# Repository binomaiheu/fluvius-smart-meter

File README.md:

# Fluvius smart meter readout project

This is my version of a readout board for the Belgian smart energy meter deployed by Fluvius. The device contains 2 ports which allow the interested hobbyist to read out the real time energy consumption every sectond P1 and the full 4kHz waveform via the S1 port. This repo is for my own education as I shamelessly copied and adapted the work of Matthijs Kooijman and Willem Aandwiel, see links below for the originals !

## Links

Below is a collection of references with the original material upon which I based this **original project** : 
* https://willem.aandewiel.nl/index.php/2018/08/28/slimme-meter-uitlezer/
* https://opencircuit.nl/blog/Slimme-meter-uitlezer 

And a few links on **github** : 

* Decoder : https://github.com/matthijskooijman/arduino-dsmr
* Logger : https://github.com/mrWheel/DSMRlogger2HTTP
* https://mrwheel.github.io/DSMRloggerWS/

You can find a **python decoder** for the serial messages here : 
* https://github.com/jvhaarst/DSMR-P1-telegram-reader

The **specs** for the smart meter can be found here : 
* https://www.netbeheernederland.nl/_upload/Files/Slimme_meter_15_a727fce1f1.pdf
* https://www.fluvius.be/sites/fluvius/files/2019-07/1901-fluvius-technical-specification-user-ports-digital-meter.pdf
* https://www.fluvius.be/sites/fluvius/files/2019-12/e-mucs_h_ed_1_3.pdf

## Hardware

### P1 port pinout

The Fluvius meter P1 port uses an RJ12 connector with the following pinout.

| pin | function     |
|-----|--------------|
| 1   | Power +5 V   |
| 2   | Data Request |
| 3   | Data GND     |
| 4   | n.c.         |
| 5   | Data line    |
| 6   | Power GND    |

The protocol is `serial TTL` between 0 and 5 V, but with *polarity reversed*, meaning that 5V indicates a `0` and 0V indicates a `1`.

### Circuit board

The circuit in the `kicad/` subfolder is essentially based on the work of Willem Aandewiel (https://opencircuit.nl/blog/Slimme-meter-uitlezer) with some modifications of my own whilst getting to know KiCad. 

I'm using a Lolin D32 ESP board (https://www.wemos.cc/en/latest/d32/index.html) to readout & process the telegrams. For the footprint i installed the following library in KiCad : 

* https://github.com/pauls-3d-things/kicad-library

This contains both the schematic as well as the footprint for the Lolin D32 board. 

### Manufacturing

See :
* https://aisler.net  for in the EU manufacturing at reasonable price

### Power

For powering the esp32 I found this post on reddit : https://www.reddit.com/r/esp32/comments/bwgn1q/how_to_power_a_lolin_d32_externally_from_a_dc/, it presents 3 options (copy pasted): 

* *I figured it out with the help of [Dave Bird's Tech Note 097](https://www.youtube.com/watch?v=yZjpYmWVLh8) which explained how the on-board regulator can be disabled (open-circuit) by tying the EN pin to ground. This allows direct application of 3.3V onto the 3V pin, powering the board directly. Additionally, if EN is held low, a USB cable can be connected and serial comms continues to operate, because the CH340C has 3.3V supply. Power from the USB is shorted to ground via 100kohm resistor, which is no big deal.*
* *An alternative is to power at 4.2V via the battery connector. The TP4054 can take up to 7V on its BAT pin, and the charger won't enable unless the voltage drops below 4.2V, so one could also supply, say, 5V via this connector. The D2 diode will protect USB.*
* *One third option is to supply 5V via VBUS pin, ensuring it is as close as possible to the USB voltage (a difference of a few tenths of a volt may not cause any problems). If paranoid, a diode can be used to protect the USB supply.*

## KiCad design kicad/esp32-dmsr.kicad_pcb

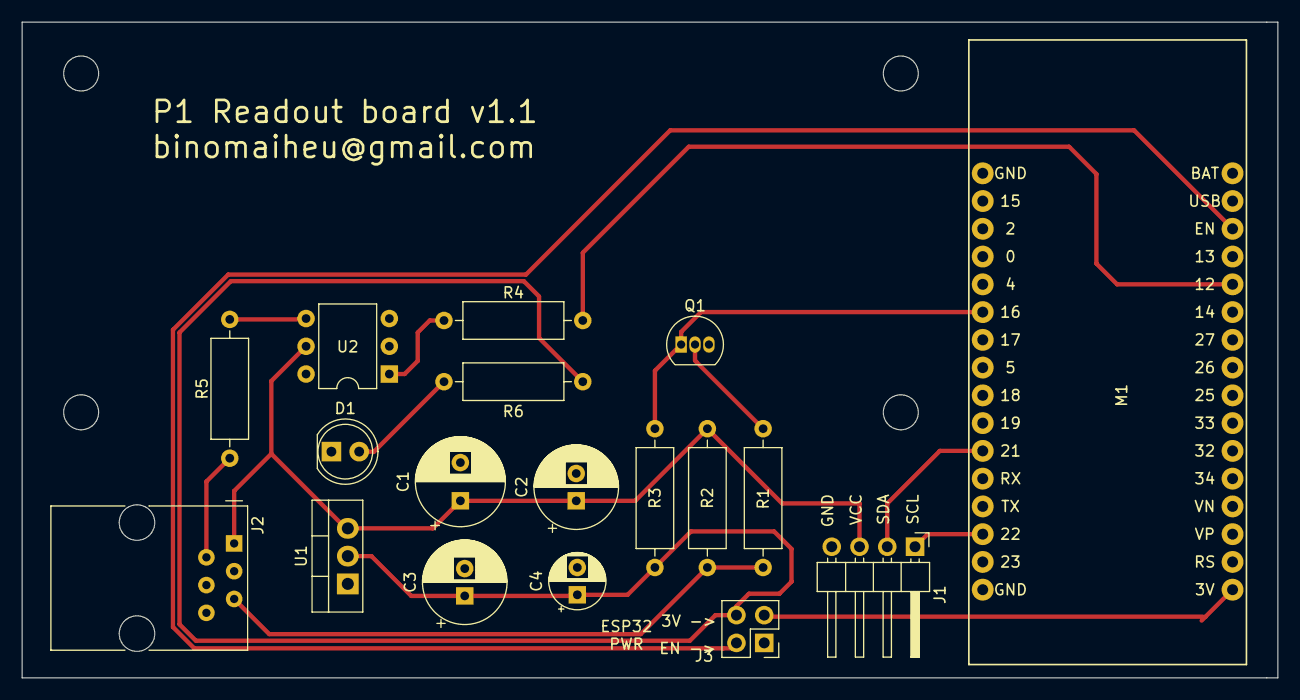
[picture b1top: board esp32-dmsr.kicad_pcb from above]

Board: 2 copper layers, 114.9 x 60.0 mm, 18 parts (0 on the bottom side), 15 nets.

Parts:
C1: 1000 µF; CP_Radial_D8.0mm_P3.50mm
C2: 1 µF; CP_Radial_D7.5mm_P2.50mm
C3: 220 µF; CP_Radial_D7.5mm_P2.50mm
C4: 2.2 µF; CP_Radial_D5.0mm_P2.50mm
D1: LED; LED_D5.0mm
J1: LCD pin header; PinHeader_1x04_P2.54mm_Horizontal
J2: RJ12; RJ12_Amphenol_54601
J3: ESP32 Power; PinHeader_2x02_P2.54mm_Vertical
M1: LolinD32
Q1: BC547; TO-92_Inline
R1: 1 kOhm; R_Axial_DIN0309_L9.0mm_D3.2mm_P12.70mm_Horizontal
R2, R3: 2.2 kOhm; R_Axial_DIN0309_L9.0mm_D3.2mm_P12.70mm_Horizontal
R4, R6: 220 Ohm; R_Axial_DIN0309_L9.0mm_D3.2mm_P12.70mm_Horizontal
R5: 10 Ohm; R_Axial_DIN0309_L9.0mm_D3.2mm_P12.70mm_Horizontal
U1: LM1085-3.3; TO-220-3_Vertical
U2: 4N35; DIP-6_W7.62mm

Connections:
5V: C1.1, C2.1, J1.3, J2.1, R2.1, U1.3, U2.5
DRQ: J2.2, R5.2
GND: C1.2, C2.2, C3.2, C4.2, D1.1, J1.4, J2.3, J2.6, J3.1, M1.17, Q1.3, U1.1, U2.2
GPIO12: M1.5, R4.2
LCD_SCL: J1.1, M1.30
LCD_SDA: J1.2, M1.27
unnamed: C3.1, C4.1, J3.4, R3.1, R6.1, U1.2
unnamed: D1.2, R6.2
unnamed: J3.2, M1.3
unnamed: J3.3, M1.16
unnamed: Q1.2, R1.2
unnamed: R4.1, U2.1
unnamed: R5.1, U2.4
RX: M1.22, Q1.1, R3.2
TX: J2.5, R1.1, R2.2

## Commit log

2021-10-22 added kicad gitignore
2021-10-22 cleanup
2021-10-22 added credits
2021-11-03 added powering options
2021-11-03 added lcd & readout
2021-11-03 added lcd
2021-11-03 version 1.1, as ordered
2022-11-27 added mqtt
